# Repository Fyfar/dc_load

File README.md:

# 🔋 DIY Electronic Load

This repository contains everything related to my **homemade electronic load** project.  
It’s a personal DIY project – not a commercial or professional design.  
I’m sharing it here mostly to keep things organized and maybe to help someone else who is experimenting with similar ideas.

---

## 📂 What's Inside

- **🖥 Firmware (ESP32)**  
  Code for controlling the load, written for **ESP32-C3 Super Mini**.  
  - No `delay()` calls (uses timers/interrupts instead)  
  - Online logging via **MQTT broker** 📡  
  - Current control via external DAC  
  - Calibration and basic measurement support  

- **📐 KiCad Files**  
  Schematics and PCB design made with KiCad.  
  Currently missing the 4-wire measurement module (will be documented later).  
  Expect changes and improvements over time.

- **📝 Notes & Experiments**  
  Test results, calibration data, and small helper scripts.

---

## 🎯 Project Goals

- Learn more about **electronics, MOSFETs, and op-amps**  
- Build a useful tool for testing power supplies and batteries  
- Experiment with **current regulation, ADC/DAC, and firmware control**  
- Try **4-wire measurements** for better accuracy  
- Keep everything DIY-friendly and fun 🚀  

---

## 🛠 Components Used

- **ADS1115** – external ADC (much more accurate than ESP32’s built-in one)  
- **MCP4725** – external DAC (better resolution and stability)  
- **4x4 Keypad** – for input  
- **PCF8575** – port expander for the keypad  
- **ESP32-C3 Super Mini** – main controller  
- **LCD 20x4 with I²C module** – display  
- **Case Z17** – enclosure  
- **80×80×15 mm 2-pin Fan** – cooling  

---

### Mermaid Diagram (rendered on GitHub)

```mermaid
flowchart TD
    ESP[ESP32-C3 Super Mini]

    ESP --> ADC["ADS1115 (ADC)"];
    ESP --> DAC["MCP4725 (DAC)"];
    ESP --> IO["PCF8575 + 4x4 Keypad"];
    ESP --> LCD["LCD 20x4 (I²C)"];
    ESP --> FAN["Cooling Fan (80x80x15, 2-pin)"];

    ADC --> MEAS[Current / Voltage Measurements];
```
---

## ⚡ Features

- Online logging with MQTT  
- External ADC & DAC for better precision  
- 4-wire measurement (documentation coming soon)  
- No blocking delays in firmware  
- Simple but expandable design  

---

## ⚠️ Disclaimer

This is a hobby project.  
I can’t guarantee correctness, safety, or reliability of the design or code.  
If you decide to use any part of it, **do it at your own risk**.

---

## 🤝 Contributions

I don’t expect pull requests, but if you’re also into DIY electronics and want to share ideas or improvements – feel free.

---

## 📜 License

MIT License – do whatever you want with the code and files, but don’t blame me if something goes wrong.

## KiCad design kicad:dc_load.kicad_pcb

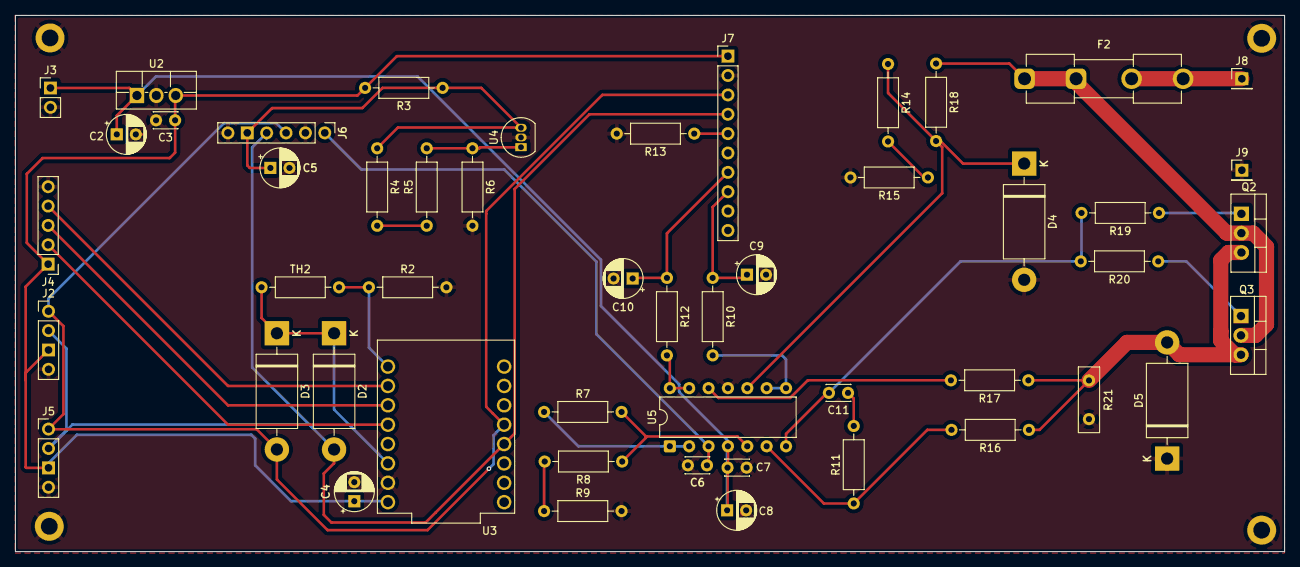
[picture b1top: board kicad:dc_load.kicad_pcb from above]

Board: 2 copper layers, 166.4 x 70.3 mm, 54 parts (0 on the bottom side), 33 nets.

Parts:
C2, C4: 220u; CP_Radial_D5.0mm_P2.50mm
C3, C6: 0.1u; C_Disc_D3.0mm_W2.0mm_P2.50mm
C5, C8: 10u; CP_Radial_D5.0mm_P2.50mm
C7: 100n; C_Disc_D3.0mm_W2.0mm_P2.50mm
C9, C10: 200n; CP_Radial_D5.0mm_P2.50mm
C11: 1n; C_Disc_D3.0mm_W2.0mm_P2.50mm
D2, D3: D_Schottky; D_DO-201AD_P15.24mm_Horizontal
D4: D; D_DO-201AD_P15.24mm_Horizontal
D5: 1N4007; D_DO-201AD_P15.24mm_Horizontal
F2: 5A; Fuseholder_Clip-5x20mm_Eaton_1A5601-01_Inline_P20.80x6.76mm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
J2: LCD socket pin; PinHeader_1x04_P2.54mm_Vertical
J3: Conn_01x02; PinHeader_1x02_P2.54mm_Vertical
J4: Encoder; PinHeader_1x05_P2.54mm_Vertical
J5: GPIO expander; PinHeader_1x04_P2.54mm_Vertical
J6: MCP4725; PinHeader_1x06_P2.54mm_Vertical
J7: ADS1115 ADC; PinHeader_1x10_P2.54mm_Vertical
J8: +; PinHeader_1x01_P2.54mm_Vertical
J9: -; PinHeader_1x01_P2.54mm_Vertical
Q2, Q3: IRLZ44N; TO-220-3_Vertical
R2: 100k; R_Axial_DIN0207_L6.3mm_D2.5mm_P10.16mm_Horizontal
R3: 200; R_Axial_DIN0207_L6.3mm_D2.5mm_P10.16mm_Horizontal
R4, R9, R15: 500; R_Axial_DIN0207_L6.3mm_D2.5mm_P10.16mm_Horizontal
R5, R8, R11, R14: 1k; R_Axial_DIN0207_L6.3mm_D2.5mm_P10.16mm_Horizontal
R6: 2k; R_Axial_DIN0207_L6.3mm_D2.5mm_P10.16mm_Horizontal
R7, R10, R12, R13, R16, R17, R18: 10k; R_Axial_DIN0207_L6.3mm_D2.5mm_P10.16mm_Horizontal
R19, R20: 100; R_Axial_DIN0207_L6.3mm_D2.5mm_P10.16mm_Horizontal
R21: 0.100; R_Box_L8.4mm_W2.5mm_P5.08mm
REF01: MH; MountingHole_2.2mm_M2_DIN965_Pad
REF02, REF03, REF04: MountingHole_2.2mm_M2_DIN965_Pad
TH2: 100k; R_Axial_DIN0207_L6.3mm_D2.5mm_P10.16mm_Horizontal
U2: L7805; TO-220F-3_Vertical
U3: ESP32-C3; MODULE_ESP32-C3_SUPERMINI
U4: TL431LP; TO-92_Inline
U5: LM324; DIP-14_W7.62mm

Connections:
+3V3: D2.1 (K), D3.1 (K), TH2.1, U3.3.3 (3V3)
+5V: C3.1, C4.1, J2.3, J4.1, J5.3, J7.1, R3.2, U2.3 (OUT), U3.5V
+12V: C2.1, C7.1, C8.1, J3.1, U2.1 (IN), U5.4 (V+)
/4.096V: C5.1, J6.5, R3.1, R4.1, U4.3 (K)
/BTN: J4.2, U3.3 (GPIO3)
/LOAD_CURR: C10.1, J7.7, R12.1
/S1: J4.4, U3.1 (GPIO1)
/S2: J4.3, U3.2 (GPIO2)
/SCL: D3.2 (A), J2.1, J5.1, J6.3, J7.3, U3.9 (GPIO9)
/SDA: D2.2 (A), J2.2, J5.2, J6.4, J7.4, U3.8 (GPIO8)
GND: C2.2, C3.2, C4.2, C5.2, C6.2, C7.2, C8.2, C9.2, C10.2, D4.2 (A), D5.1 (K), J2.4, J3.2, J4.5, J5.4, J6.2, J6.6, J7.2, J9.1, R2.2, R6.2, R9.2, R13.2, R15.2, R21.2, REF01.1, REF02.1, REF03.1, REF04.1, U2.2 (GND), U3.G (GND), U4.2 (A), U5.11 (V-)
unnamed: C11.1, R11.2
unnamed: C11.2, R19.2, R20.2, U5.7
unnamed: D4.1 (K), R14.1, R18.2, U5.10 (+)
unnamed: D5.2 (A), Q2.3 (S), Q3.3 (S), R16.1, R17.1, R21.1
unnamed: C6.1, J6.1, U5.3 (+)
unnamed: J7.5, R13.1
unnamed: C9.1, J7.8, R10.1
unnamed: F2.2, J8.1
unnamed: F2.1, Q2.2 (D), Q3.2 (D), R18.1
unnamed: Q2.1 (G), R19.1
unnamed: Q3.1 (G), R20.1
unnamed: R4.2, R5.1
unnamed: R8.2, R9.1
unnamed: R14.2, R15.1
unnamed: R2.1, TH2.2, U3.0 (GPIO0)
unnamed: R5.2, R6.1, U4.1 (REF)
unnamed: R7.1, U5.1, U5.2 (-)
unnamed: R7.2, R8.1, U5.5 (+)
unnamed: R11.1, R16.2, U5.6 (-)
unnamed: R10.2, U5.8, U5.9 (-)
unnamed: R17.2, U5.12 (+)
unnamed: R12.2, U5.13 (-), U5.14

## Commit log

2025-04-04 Init commit of dc load
2025-04-13 Resized PCB and added some caps
2025-08-18 Added firmware for esp32
2025-08-18 Added kicad folder
2026-06-11 Rename to dc_load, move credentials to secrets.h, clean up tracked junk
    - Rename current_source.ino -> dc_load.ino, current_source.code-workspace -> dc_load.code-workspace
    - Replace hardcoded WiFi/MQTT credentials with #include "secrets.h" (gitignored)
    - Add secrets.h.example as a template
    - Untrack auto-generated VSCode files with absolute paths (launch.json, c_cpp_properties.json)
    - Untrack KiCad lock/autosave files; add gitignore patterns for them
    - Fix .code-workspace to use relative path instead of absolute /Users/fyfar/...
